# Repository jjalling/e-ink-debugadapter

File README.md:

# e-ink-debugadapter
Simple debug adapter for Waveshare e-ink

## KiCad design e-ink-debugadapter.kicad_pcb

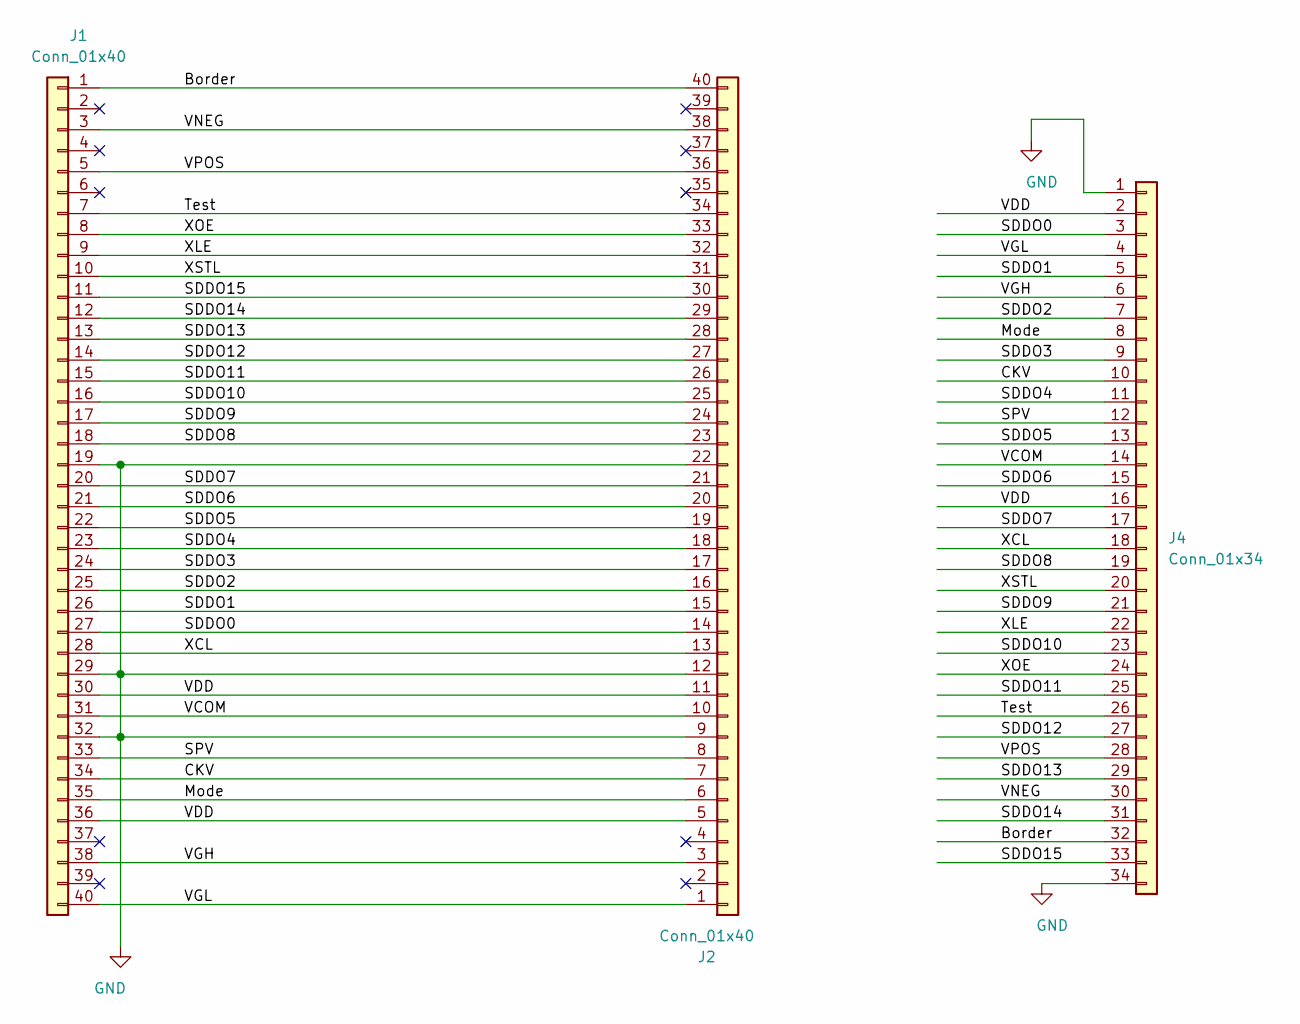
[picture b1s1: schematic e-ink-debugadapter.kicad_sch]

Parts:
J1, J2: Conn_01x40; AMPHENOL-F31L-1A7H1-11040
J4: Conn_01x34; PinHeader_2x17_P2.54mm_Vertical

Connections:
/Border: J1.1, J2.40, J4.32
/CKV: J1.34, J2.7, J4.10
/Mode: J1.35, J2.6, J4.8
/SDDO0: J1.27, J2.14, J4.3
/SDDO1: J1.26, J2.15, J4.5
/SDDO2: J1.25, J2.16, J4.7
/SDDO3: J1.24, J2.17, J4.9
/SDDO4: J1.23, J2.18, J4.11
/SDDO5: J1.22, J2.19, J4.13
/SDDO6: J1.21, J2.20, J4.15
/SDDO7: J1.20, J2.21, J4.17
/SDDO8: J1.18, J2.23, J4.19
/SDDO9: J1.17, J2.24, J4.21
/SDDO10: J1.16, J2.25, J4.23
/SDDO11: J1.15, J2.26, J4.25
/SDDO12: J1.14, J2.27, J4.27
/SDDO13: J1.13, J2.28, J4.29
/SDDO14: J1.12, J2.29, J4.31
/SDDO15: J1.11, J2.30, J4.33
/SPV: J1.33, J2.8, J4.12
/Test: J1.7, J2.34, J4.26
/VCOM: J1.31, J2.10, J4.14
/VDD: J1.30, J1.36, J2.5, J2.11, J4.2, J4.16
/VGH: J1.38, J2.3, J4.6
/VGL: J1.40, J2.1, J4.4
/VNEG: J1.3, J2.38, J4.30
/VPOS: J1.5, J2.36, J4.28
/XCL: J1.28, J2.13, J4.18
/XLE: J1.9, J2.32, J4.22
/XOE: J1.8, J2.33, J4.24
/XSTL: J1.10, J2.31, J4.20
GND: J1.19, J1.29, J1.32, J2.9, J2.12, J2.22, J4.1, J4.34

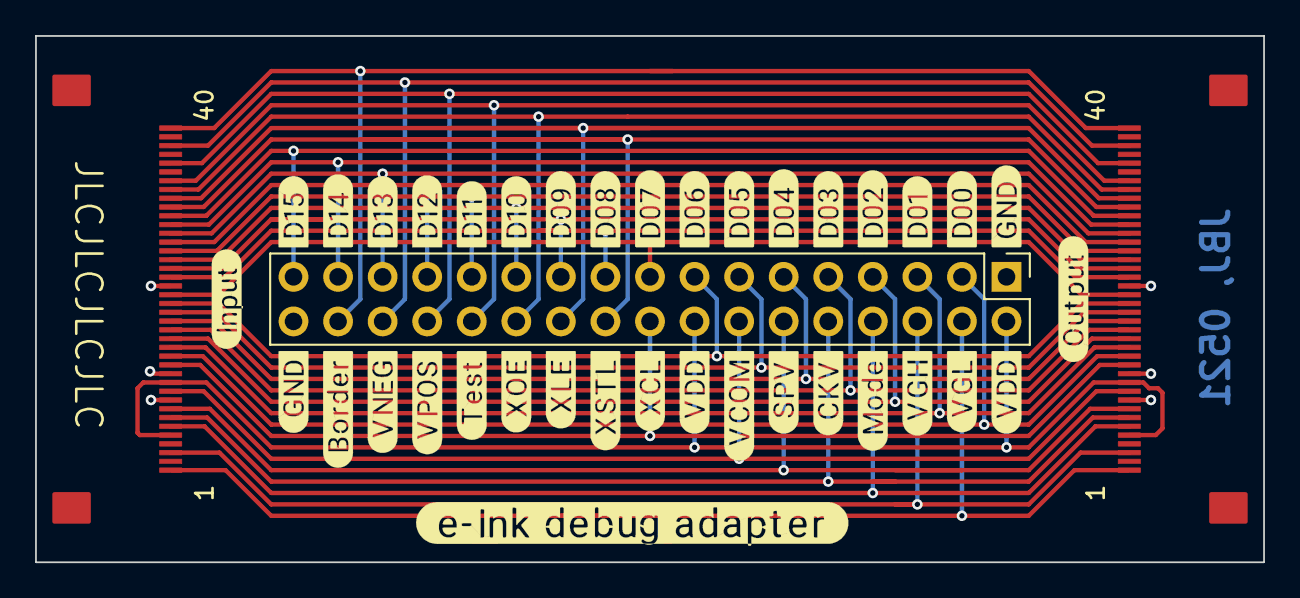
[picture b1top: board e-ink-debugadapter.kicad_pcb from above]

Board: 2 copper layers, 70.0 x 30.0 mm, 3 parts (0 on the bottom side), 32 nets.

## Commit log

2021-05-07 Simple debug adapter
